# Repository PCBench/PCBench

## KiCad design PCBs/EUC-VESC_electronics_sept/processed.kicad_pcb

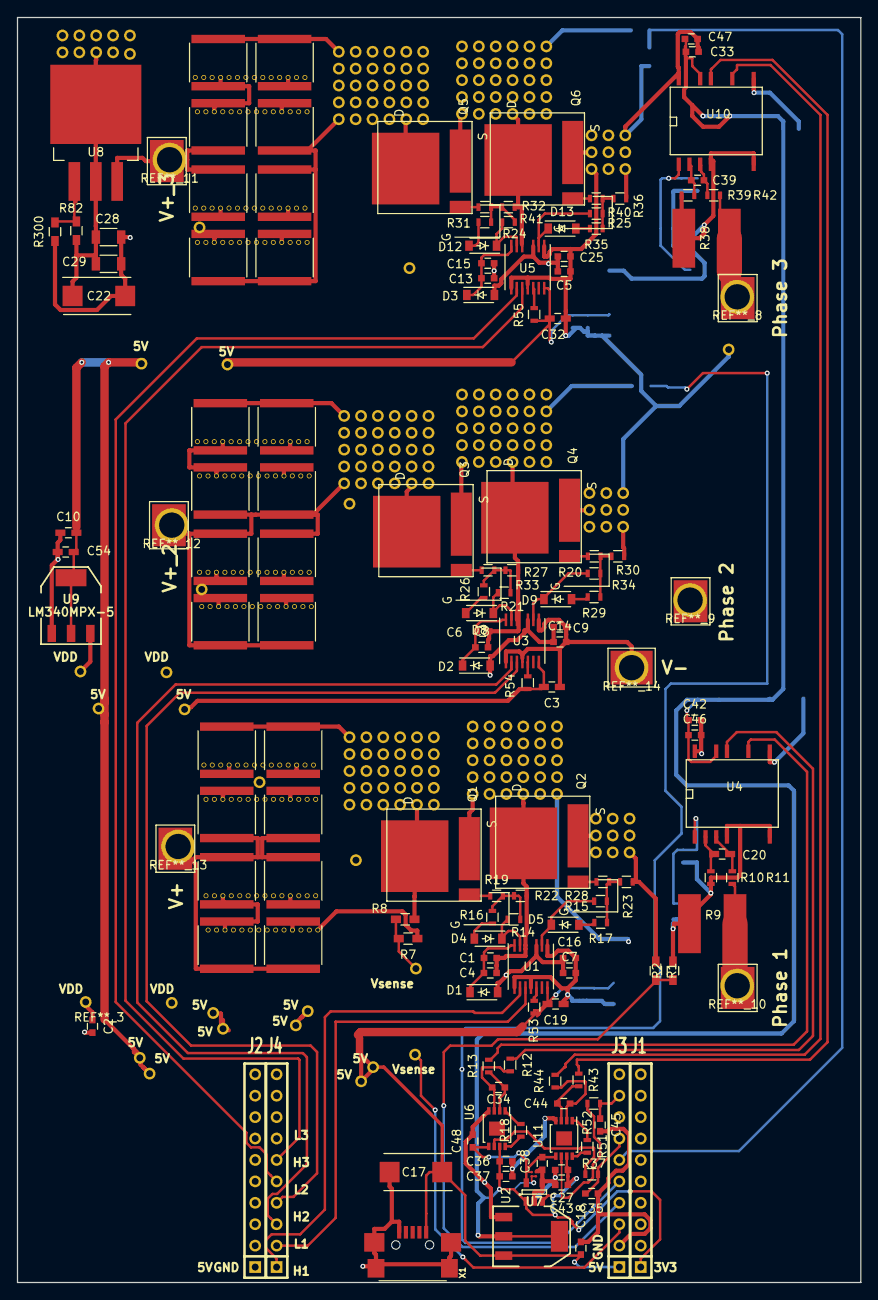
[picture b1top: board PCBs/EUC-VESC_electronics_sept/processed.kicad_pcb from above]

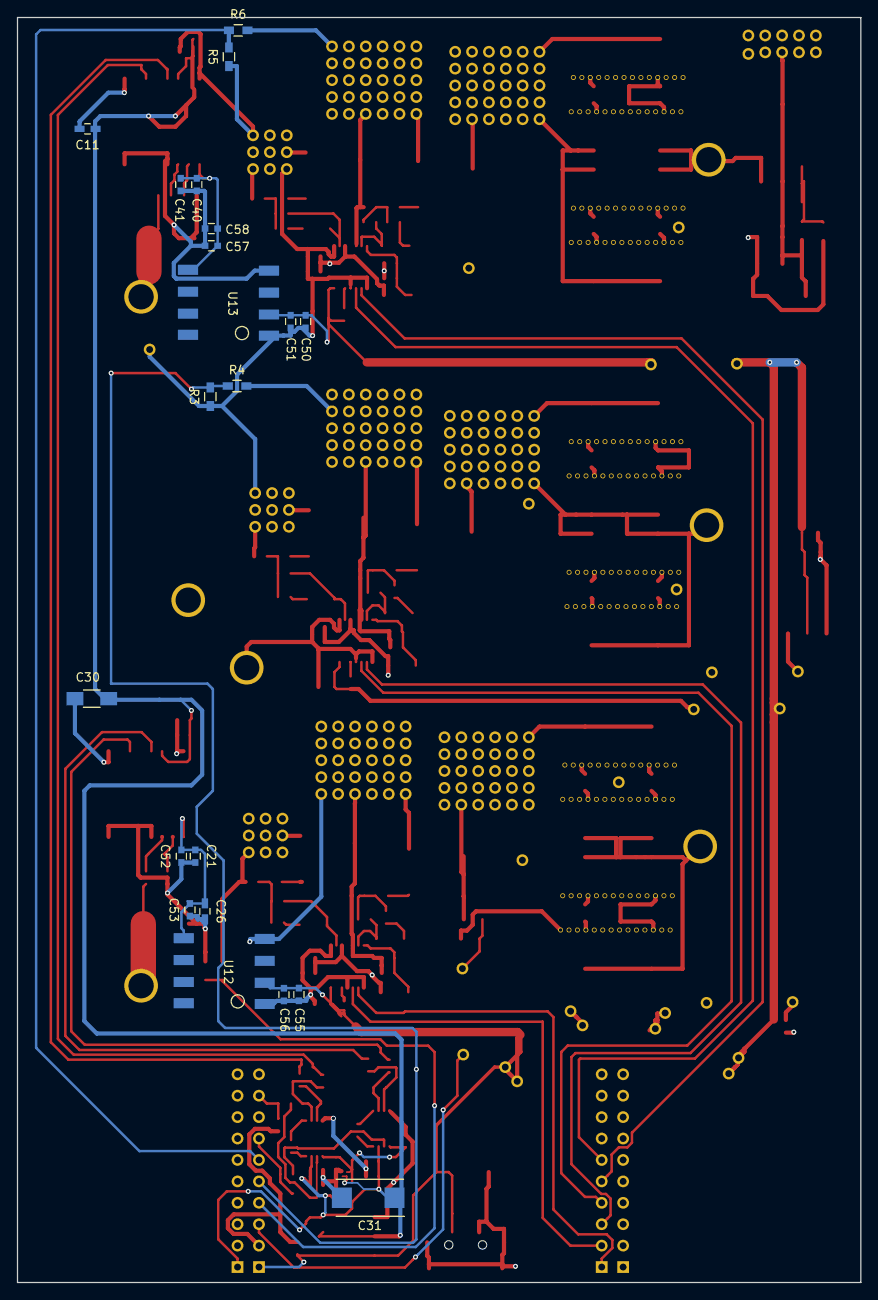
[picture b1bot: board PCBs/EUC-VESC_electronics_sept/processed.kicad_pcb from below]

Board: 4 copper layers, 100.0 x 150.0 mm, 169 parts (21 on the bottom side), 74 nets.

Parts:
C1, C2, C6, C7, C13, C14, C25, C33, C36, C38, C41, C43, C46, C48, C50, C53, C55, C58: 0.1uf; C_0603
C3, C10, C19, C26, C32: 0.1uf; C_0603_HandSoldering
C4, C16: 2.2uf; C_0603
C5, C8, C9, C15: 2.2; C_0603
C11: 1uf; C_0603_HandSoldering
C17, C22, C31: 100uf; TantalC_SizeD_EIA-7343_Reflow
C18, C21, C27, C37, C40, C42, C47, C51, C52, C56, C57: 10uf; C_0603
C20: 33nf; C_0603_HandSoldering
C28, C29: 10uf; C_1206
C30: 2.2uf; C_1206_HandSoldering
C34, C44: 4.7nf; C_0603
C35, C45: 100pf; C_0603
C39: 33nf; C_0603
C49, C49_2, C49_3, C49_4, C49_5, C49_6, C49_7, C49_8, C49_9, C49_10, C49_11, C49_12, C49_13, C49_14, C49_15, C49_16, C49_17, C49_18, C49_19, C49_20, C49_21, C49_22, C49_23, C49_24: 15uf; C_2225_invis
C54: 10uf; C_0603_HandSoldering
D1, D2, D3: DFLS1150-7; SOD-123
D4, D5, D8, D9, D12, D13: D_Schottky_Small; SOD-123
J1: Ti_Booster_40_J1; SIL-10J1
J2: Ti_Booster_40_J2; SIL-10J2
J3: Ti_Booster_40_J3; SIL-10J3
J4: Ti_Booster_40_J4; SIL-10J4
Phase 1: MOTOR3; 1PAD_4x5mm
Phase 2: MOTOR2; 1PAD_4x5mm
Phase 3: MOTOR1; 1PAD_4x5mm
Q1, Q2, Q3, Q4, Q5, Q6: FDMT-800; P-PG-HSOF-08
R1, R3, R5, R7: 1.3K; R_0603_HandSoldering
R2, R4, R6, R8: 39K; R_0603_HandSoldering
R9, R38: 0.001R; shunt_ERJ-MS6SF1M0U
R10, R11, R37, R39, R42, R52: 20R; R_0603
R12, R13, R43, R44: R20; R_0603
R14, R15, R20, R21, R24, R25: 10R; R_0603
R16, R17, R26, R29, R31, R35: R4; R_0603
R18, R51: 10Mr; R_0603
R19, R28, R33, R34, R40, R41: ferrite; R_0603
R22, R23, R27, R30, R32, R36: R39k; R_0603
R53, R54, R55: r20; R_0603
R82: R; R_0603_HandSoldering
R300: R_Small; R_0603_HandSoldering
U1, U3, U5: ADuM7223; LGA-13
U2: TPS72116DBVR; SOT-23-5
U4, U10: SI8920; SI_8920SO-16
U6, U11: ad623; MSOP-8-1EP_3x3mm_Pitch0.65mm
U7: NCP1117ST33T3G; SOT-223
U8: tl783; TO-263-3Lead
U9: LM340MPX-5; SOT223_bcp53
U12, U13: R1SE-0505-R; recom_power
V+: IN+; 1PAD_4x5mm
V+_2, V+_3: IN+; 1PAD_4x5mm
V-: IN-; 1PAD_4x5mm
X1: MINI-USB-SCHIELD-32005-201; USB-UX60R-MB-5ST

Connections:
+1V5: C38.1, C48.1, U2.5, U6.5, U11.5
+3V3: C11.1, C27.1, C30.1, C31.1, C33.1, C36.1, C37.1, C42.1, C43.1, C46.1, C47.1, J1.1, U2.1, U2.3, U4.8, U6.7, U7.2, U10.8, U11.7
+5V: C3.2, C10.2, C17.1, C18.1, C19.2, C32.1, C50.2, C51.2, C54.1, C55.2, C56.2, J3.1, R53.2, R54.2, R55.2, U1.7, U3.7, U5.7, U7.3, U9.3, U12.2, U13.2, X1.1
+5VA: C21.1, C26.1, C52.2, C53.2, U4.1, U12.5
+5VD: C40.1, C41.1, C57.2, C58.2, U10.1, U13.5
/Power MOSFETS/CurrentA: C35.1, J3.7, R37.1
/Power MOSFETS/CurrentC: C45.1, J3.9, R52.1
/Power MOSFETS/H2_VS: C6.2, C8.2, Phase 2.1, Q3.2, Q4.1, R4.2, R27.1, U3.11
/Power MOSFETS/M_H1: J4.1, U1.2
/Power MOSFETS/M_H2: J4.3, U3.2
/Power MOSFETS/M_H3: J4.5, U5.2
/Power MOSFETS/M_L1: J4.2, U1.3
/Power MOSFETS/M_L2: J4.4, U3.3
/Power MOSFETS/M_L3: J4.6, U5.3
/Power MOSFETS/PHASE_1: Phase 1.1, R9.1, R11.2
/Power MOSFETS/PHASE_3: Phase 3.1, R38.1, R42.2
/Power MOSFETS/sense1_N: R13.2, U4.6
/Power MOSFETS/sense1_P: R12.2, U4.7
/Power MOSFETS/sense2_N: R44.2, U10.6
/Power MOSFETS/sense2_P: R43.2, U10.7
GND: C2.2, C3.1, C5.2, C7.2, C9.2, C10.1, C11.2, C14.2, C16.2, C17.2, C18.2, C19.1, C22.2, C25.2, C27.2, C28.1, C29.1, C30.2, C31.2, C32.2, C33.2, C35.2, C36.2, C37.2, C38.2, C42.2, C43.2, C45.2, C46.2, C47.2, C48.2, C49.2, C49_2.2, C49_3.2, C49_4.2, C49_5.2, C49_6.2, C49_7.2, C49_8.2, C49_9.2, C49_10.2, C49_11.2, C49_12.2, C49_13.2, C49_14.2, C49_15.2, C49_16.2, C49_17.2, C49_18.2, C49_19.2, C49_20.2, C49_21.2, C49_22.2, C49_23.2, C49_24.2, C50.1, C51.1, C54.2, C55.1, C56.1, J2.1, J3.2, Q2.2, Q4.2, Q6.2, R1.1, R3.1, R5.1, R7.1, R23.1, R30.1, R36.1, R300.2, U1.1, U1.4, U1.8, U2.2, U2.4, U3.1, U3.4, U3.8, U4.5, U5.1, U5.4, U5.8, U6.4, U7.1, U9.2, U10.5, U11.4, U12.1, U13.1, V-.1, X1.5
GNDA: C1.2, C4.2, C21.2, C26.2, C52.1, C53.1, Q1.2, Q2.1, R2.2, R9.2, R10.2, R22.1, U1.11, U4.4, U12.4
GNDD: C13.2, C15.2, C40.2, C41.2, C57.1, C58.1, Q5.2, Q6.1, R6.2, R32.1, R38.2, R39.2, U5.11, U10.4, U13.4
unnamed: C1.1, C4.1, D1.1, U1.13
unnamed: C6.1, C8.1, D2.1, U3.13
unnamed: C13.1, C15.1, D3.1, U5.13
unnamed: C20.1, R10.1, U4.2
unnamed: C20.2, R11.1, U4.3
unnamed: C34.1, R12.1, U6.3
unnamed: C34.2, R13.1, U6.2
unnamed: C39.1, R39.1, U10.2
unnamed: C39.2, R42.1, U10.3
unnamed: C44.1, R43.1, U11.3
unnamed: C44.2, R44.1, U11.2
unnamed: D4.1, R14.2, U1.12
unnamed: D4.2, R16.2
unnamed: D5.1, R15.1, U1.9
unnamed: D5.2, R17.2
unnamed: D8.1, R21.1, U3.12
unnamed: D8.2, R26.2
unnamed: D9.1, R20.1, U3.9
unnamed: D9.2, R29.2
unnamed: D12.1, R24.1, U5.12
unnamed: D12.2, R31.2
unnamed: D13.1, R25.1, U5.9
unnamed: D13.2, R35.2
unnamed: J3.3, R7.2, R8.1
unnamed: J3.4, R1.2, R2.1
unnamed: J3.5, R3.2, R4.1
unnamed: J3.6, R5.2, R6.1
unnamed: Q1.3, R19.1
unnamed: Q2.3, R28.2
unnamed: Q3.3, R33.1
unnamed: Q4.3, R34.1
unnamed: Q5.3, R41.1
unnamed: Q6.3, R40.1
unnamed: R14.1, R16.1, R19.2, R22.2
unnamed: R15.2, R17.1, R23.2, R28.1
unnamed: R18.1, U6.8
unnamed: R18.2, U6.1
unnamed: R20.2, R29.1, R30.2, R34.2
unnamed: R21.2, R26.1, R27.2, R33.2
unnamed: R24.2, R31.1, R32.2, R41.2
unnamed: R25.2, R35.1, R36.2, R40.2
unnamed: R37.2, U6.6
unnamed: R51.1, U11.8
unnamed: R51.2, U11.1
unnamed: R52.2, U11.6
unnamed: R53.1, U1.5
unnamed: R54.1, U3.5
unnamed: R55.1, U5.5
unnamed: R82.2, R300.1, U8.1
VDD: C2.1, C5.1, C7.1, C9.1, C14.1, C16.1, C22.1, C25.1, C28.2, C29.2, D1.2, D2.2, D3.2, R82.1, U1.10, U3.10, U5.10, U8.2, U8.4, U9.1
V_SUPPLY: C49.1, C49_2.1, C49_3.1, C49_4.1, C49_5.1, C49_6.1, C49_7.1, C49_8.1, C49_9.1, C49_10.1, C49_11.1, C49_12.1, C49_13.1, C49_14.1, C49_15.1, C49_16.1, C49_17.1, C49_18.1, C49_19.1, C49_20.1, C49_21.1, C49_22.1, C49_23.1, C49_24.1, Q1.1, Q3.1, Q5.1, R8.2, U8.3, V+.1, V+_2.1, V+_3.1

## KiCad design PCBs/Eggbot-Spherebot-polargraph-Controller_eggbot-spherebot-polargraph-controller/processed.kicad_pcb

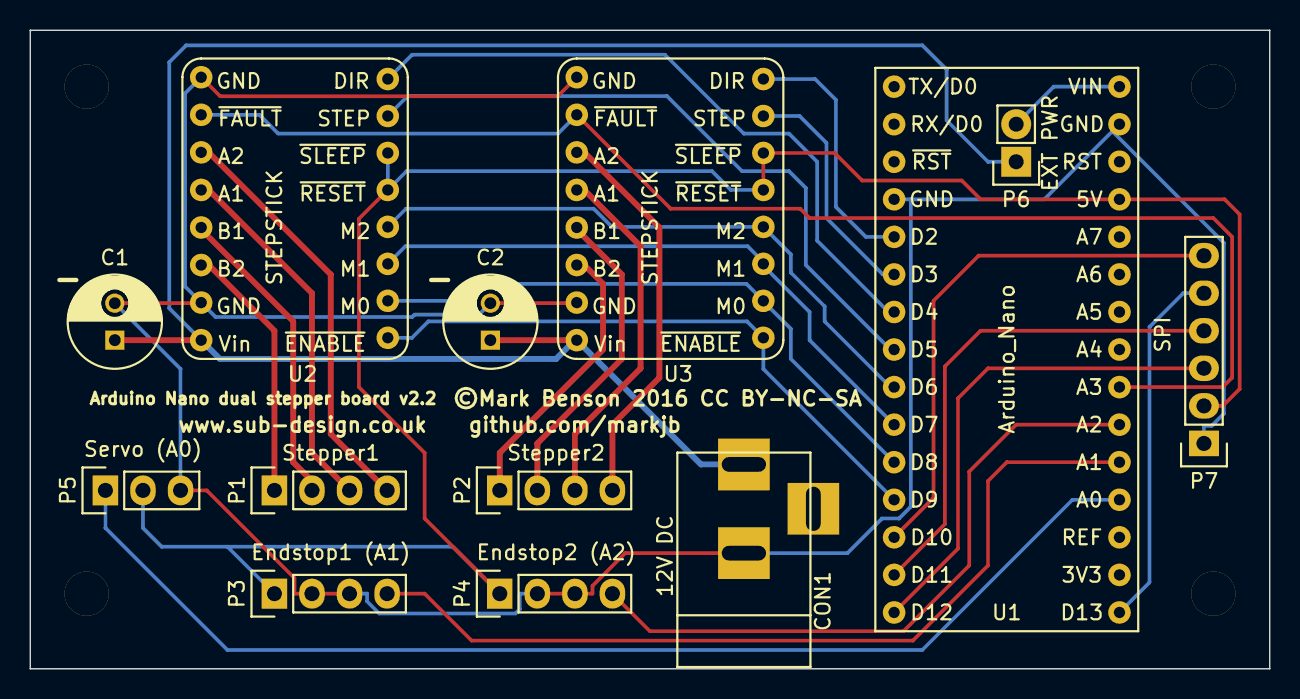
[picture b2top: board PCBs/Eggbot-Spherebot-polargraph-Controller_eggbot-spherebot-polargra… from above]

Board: 2 copper layers, 83.8 x 43.2 mm, 13 parts (0 on the bottom side), 28 nets.

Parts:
C1, C2: CP; C_Radial_D6.3_L11.2_P2.5
CON1: 12V DC; BARREL_JACK
P1: Stepper1; Pin_Header_Straight_1x04
P2: Stepper2; Pin_Header_Straight_1x04
P3: Endstop1 (A1); Pin_Header_Straight_1x04
P4: Endstop2 (A2); Pin_Header_Straight_1x04
P5: Servo (A0); Pin_Header_Straight_1x03
P6: EXT PWR; Pin_Header_Straight_1x02
P7: SPI; Pin_Header_Straight_1x06
U1: Arduino_Nano; Arduino_nano_v3
U2, U3: STEPSTICK; Stepstick

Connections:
+12V: C1.1, C2.1, CON1.1, P6.1, U2.8, U3.8
/DIR1: U1.7, U2.16
/DIR2: U1.5, U3.16
/ENABLE: U1.12, U2.9, U3.9
/ESTOP1: P3.4, U1.20
/ESTOP2: P4.4, U1.21
/FAULT: U1.22, U2.2, U3.2
/M0: U1.11, U2.10, U3.10
/M1: U1.10, U2.11, U3.11
/M2: U1.9, U2.12, U3.12
/MISO: P7.3, U1.15
/MOSI: P7.4, U1.14
/SCK: P7.5, U1.16
/SD_SEL: P7.6, U1.13
/SERVO: P5.1, U1.19
/STEP1: U1.8, U2.15
/STEP2: U1.6, U3.15
/VCC: P3.1, P4.1, P5.2, P7.2, U1.27, U2.13, U2.14, U3.13, U3.14
GND: C1.2, C2.2, CON1.2, P3.2, P3.3, P4.2, P4.3, P5.3, P7.1, U1.4, U1.29, U2.1, U2.7, U3.1, U3.7
unnamed: P1.1, U2.6
unnamed: P1.2, U2.5
unnamed: P1.3, U2.4
unnamed: P1.4, U2.3
unnamed: P2.1, U3.6
unnamed: P2.2, U3.5
unnamed: P2.3, U3.4
unnamed: P2.4, U3.3
unnamed: P6.2, U1.30

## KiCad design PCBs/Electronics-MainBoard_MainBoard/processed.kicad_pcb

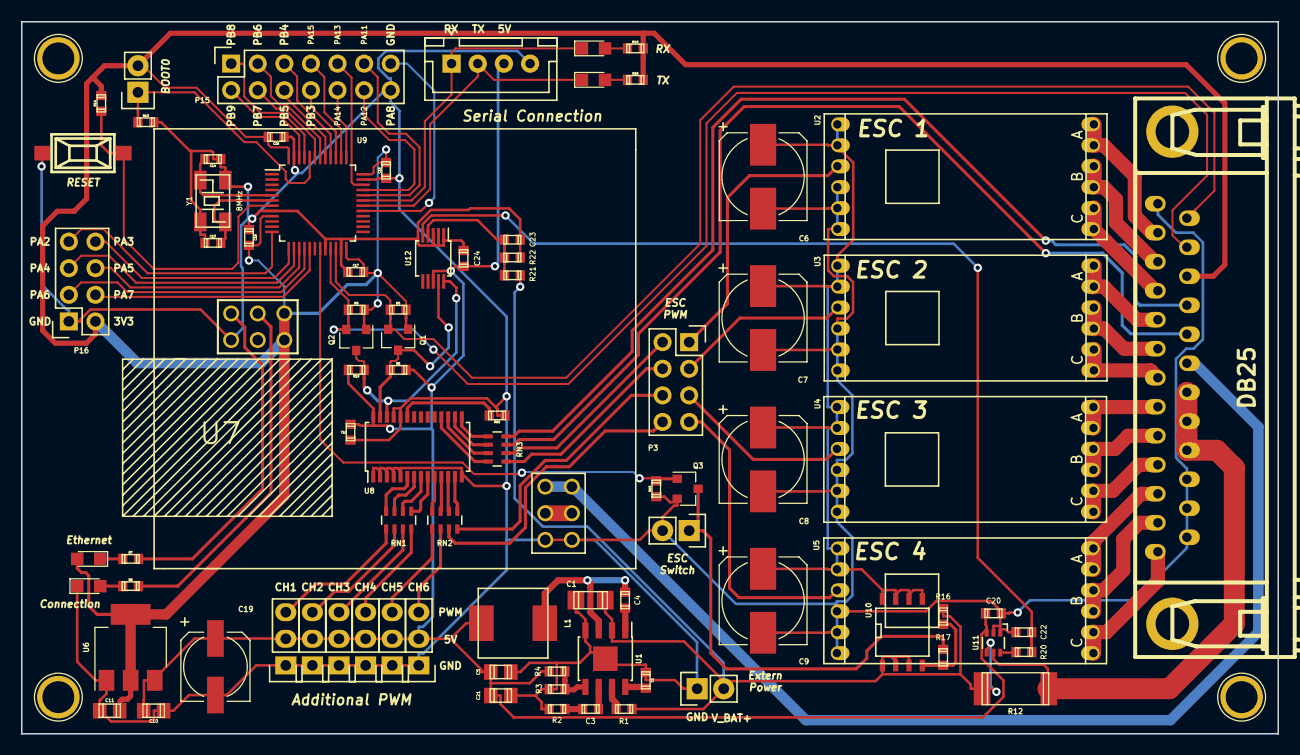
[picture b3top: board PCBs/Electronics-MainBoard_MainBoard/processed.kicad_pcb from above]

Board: 2 copper layers, 120.0 x 68.0 mm, 89 parts (0 on the bottom side), 96 nets.

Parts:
C1: 10uF/25V; c_1206
C2, C20, C23, C24: 0.1uF; c_0603
C3: 3.9nF; c_0603
C4: 10nF; c_0603
C5, C21: 22uF/10V; c_0805
C6, C7, C8, C9: 220uF/25V; CP_Elec_8x10
C10, C11: 1uF; c_0805
C12: 10uF; c_0603
C13, C14: 33pF; c_0603
C15, C16, C17, C18, C22: 1uF; c_0603
C19: 220uF/10V; CP_Elec_6.3x5.8
D1, D2, D3, D4: LED; LED_0805
J1: DB25; DB_25M
L1: 10uH/4A; ASPI-0630LR
P1: BOOT; Socket_Strip_Straight_1x02
P2: CONN_01X04; JST_XH_B04B-XH-A_04x2.50mm_Straight
P3, P16: CONN_02X04; Socket_Strip_Straight_2x04
P4, P5, P6, P7: HOLE; 1pin
P8, P14: CONN_01X02; Socket_Strip_Straight_1x02
P9, P10, P11, P12, P13, P18: CONN_01X03; Socket_Strip_Straight_1x03
P15: CONN_02X07; Socket_Strip_Straight_2x07
Q1, Q2: BSS138; SOT-23
Q3: DMN65D8L; SOT-23
R1: 100k; r_0603
R2: 6.8k; r_0603
R3: 10k 1%; r_0603
R4: 44.2k 1%; r_0603
R5, R8, R9, R10, R11, R13, R14, R15, R16: 10k; r_0603
R6, R7, R18, R19: 330; r_0603
R12: 0.003 %1; r_2512
R17: 1k; r_0603
R20: 3.3k; r_0603
R21: 30.1k %1; r_0603
R22: 10k %1; r_0603
RN1, RN2, RN3: 20k; R_Array_Concave_4x0603
SW1: RESET; smd_push
U1: mp2307; SOIC-8-1EP_3.9x4.9mm_Pitch1.27mm
U2, U3, U4, U5: DYS_mini_ESC; DYS_Mini_ESC
U6: TLV1117LV33; SOT-223
U7: TENDA_P200; Tenda_p200
U8: pca9685; TSSOP-28_4.4x9.7mm_Pitch0.65mm
U9: STM32F103CBT6; LQFP-48_7x7mm_Pitch0.5mm
U10: SI4425DDY; SOIC-8-N
U11: INA199A2; SC-70-6
U12: ADS1015; MSOP-10_3x3mm_Pitch0.5mm
Y1: 8MHz; crystal_maple

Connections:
/3V3: C11.1, C15.1, C16.1, C17.1, C18.1, D2.2, J1.23, P1.2, P16.2, Q1.1, Q2.1, R5.1, R9.1, R14.1, R18.1, R19.1, U6.2, U6.4, U7.3V3, U9.9, U9.24, U9.36, U9.48
/5V: C5.1, C10.1, C12.1, C19.1, C20.1, C21.1, C24.1, L1.2, P2.3, P9.2, P10.2, P11.2, P12.2, P13.2, P18.2, R4.1, R8.1, R10.1, U6.3, U8.28, U11.3, U12.8
/ADC_I: C22.1, R20.1, U12.5
/ADC_V: C23.1, R21.2, R22.1, U12.4
/CH0: P9.3, RN1.1
/CH1: P10.3, RN1.2
/CH2: P11.3, RN1.3
/CH3: P12.3, RN1.4
/CH4: P13.3, RN2.1
/CH5: P18.3, RN2.2
/CH6: P3.8, RN2.3
/CH7: P3.6, RN2.4
/CH10: P3.2, RN3.6
/CH11: P3.4, RN3.5
/ESC1: P3.1, U2.2
/ESC2: P3.3, U3.2
/ESC3: P3.5, U4.2
/ESC4: P3.7, U5.2
/LED1: J1.21, RN3.7
/LED2: J1.22, RN3.8
/MOTOR_1A: J1.12, U2.4
/MOTOR_1B: J1.11, U2.5
/MOTOR_1C: J1.10, U2.6
/MOTOR_2A: J1.9, U3.4
/MOTOR_2B: J1.8, U3.5
/MOTOR_2C: J1.7, U3.6
/MOTOR_3A: J1.6, U4.4
/MOTOR_3B: J1.5, U4.5
/MOTOR_3C: J1.4, U4.6
/MOTOR_4A: J1.3, U5.4
/MOTOR_4B: J1.2, U5.5
/MOTOR_4C: J1.1, U5.6
/OSC_N: C14.1, U9.5, Y1.2
/OSC_P: C13.1, U9.6, Y1.1
/PA2: P16.7, U9.12
/PA3: P16.8, U9.13
/PA4: P16.5, U9.14
/PA5: P16.6, U9.15
/PA6: P16.3, U9.16
/PA7: P16.4, U9.17
/PA8: P15.13, U9.29
/PA11: P15.11, U9.32
/PA12: P15.12, U9.33
/PA13: P15.9, U9.34
/PA14: P15.10, U9.37
/PA15: P15.7, U9.38
/PB3: P15.8, U9.39
/PB4: P15.5, U9.40
/PB5: P15.6, U9.41
/PB6: P15.3, U9.42
/PB7: P15.4, U9.43
/PB8: P15.1, U9.45
/PB9: P15.2, U9.46
/PWR_SW: Q3.1, R15.1, U9.19
/RX1: D4.1, P2.1, U9.31
/SCL_3V3: J1.24, Q2.2, R9.2, U9.21
/SCL_5V: Q2.3, R10.2, U8.26, U12.10
/SDA_3V3: J1.25, Q1.2, R5.2, U9.22
/SDA_5V: Q1.3, R8.2, U8.27, U12.9
/T+: J1.20, U7.T_+
/TX1: D3.1, P2.2, U9.30
/V_BAT: C1.1, P8.2, R1.1, R12.1, R16.1, R21.1, U1.2, U10.1, U10.2, U10.3, U11.4
/V_IN: J1.17, J1.18, J1.19, R12.2, U11.5
/V_PWR: C6.1, C7.1, C8.1, C9.1, U2.3, U3.3, U4.3, U5.3, U10.5, U10.6, U10.7, U10.8
GND: C1.2, C2.2, C5.2, C6.2, C7.2, C8.2, C9.2, C10.2, C11.2, C12.2, C13.2, C14.2, C15.2, C16.2, C17.2, C18.2, C19.2, C20.2, C21.2, C22.2, C23.2, C24.2, D1.1, J1.13, J1.14, J1.15, J1.16, P2.4, P8.1, P9.1, P10.1, P11.1, P12.1, P13.1, P14.2, P15.14, P16.1, P18.1, Q3.2, R2.2, R3.2, R11.2, R13.1, R15.2, R22.2, SW1.1, U1.4, U1.9, U2.1, U3.1, U4.1, U5.1, U6.1, U7.GND, U7.T_-, U8.1, U8.2, U8.3, U8.4, U8.5, U8.14, U8.24, U8.25, U9.8, U9.20, U9.23, U9.35, U9.47, U11.1, U11.2, U12.1, U12.2, U12.3, Y1.3
unnamed: C2.1, U1.8
unnamed: C3.1, U1.6
unnamed: C3.2, R2.1
unnamed: C4.1, L1.1, U1.3
unnamed: C4.2, U1.1
unnamed: D1.2, R6.2
unnamed: D2.1, R7.2
unnamed: D3.2, R18.2
unnamed: D4.2, R19.2
unnamed: P1.1, R13.2, U9.44
unnamed: P14.1, Q3.3, R17.2
unnamed: R1.2, U1.7
unnamed: R3.1, R4.2, U1.5
unnamed: R6.1, U7.C
unnamed: R7.1, U7.E
unnamed: R11.1, U8.23
unnamed: R14.2, SW1.2, U9.7
unnamed: R16.2, R17.1, U10.4
unnamed: R20.2, U11.6
unnamed: RN1.5, U8.9
unnamed: RN1.6, U8.8
unnamed: RN1.7, U8.7
unnamed: RN1.8, U8.6
unnamed: RN2.5, U8.13
unnamed: RN2.6, U8.12
unnamed: RN2.7, U8.11
unnamed: RN2.8, U8.10
unnamed: RN3.1, U8.15
unnamed: RN3.2, U8.16
unnamed: RN3.3, U8.17
unnamed: RN3.4, U8.18

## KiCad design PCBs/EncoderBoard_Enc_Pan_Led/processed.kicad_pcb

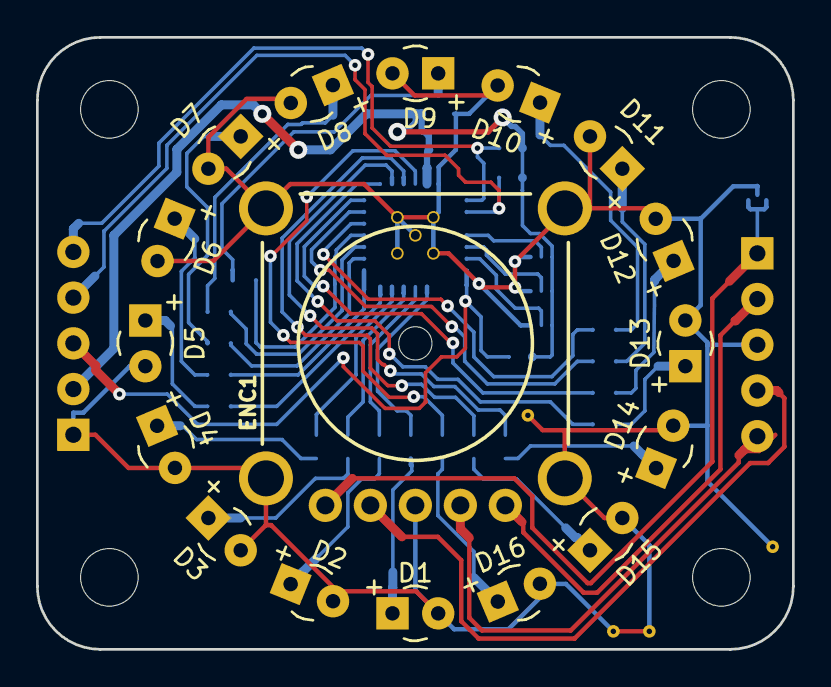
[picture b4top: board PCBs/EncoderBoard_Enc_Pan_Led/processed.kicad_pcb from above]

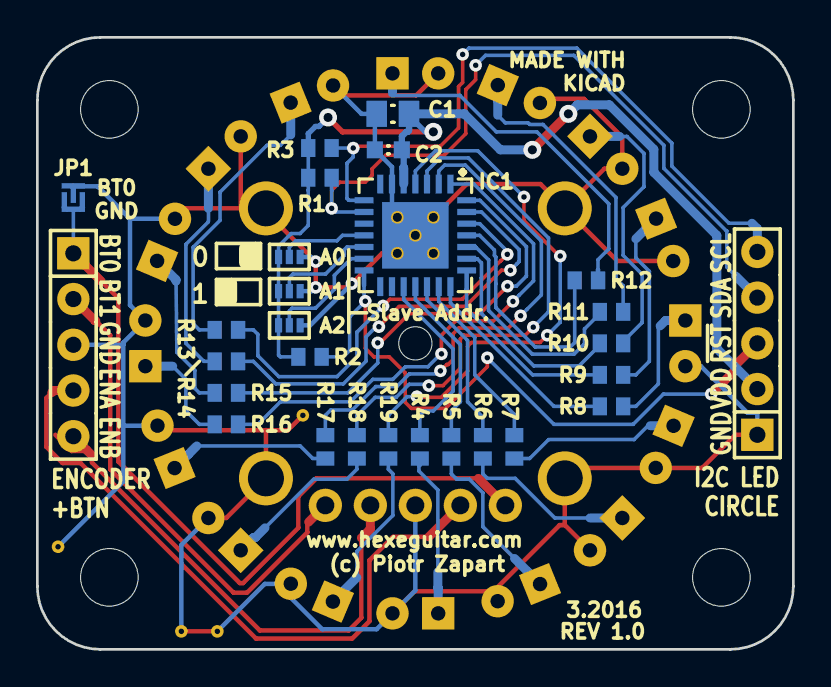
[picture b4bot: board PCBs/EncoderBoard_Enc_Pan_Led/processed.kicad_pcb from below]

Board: 2 copper layers, 42.0 x 34.0 mm, 58 parts (28 on the bottom side), 44 nets.

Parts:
C1: 10µ; CAPC_0805_2012X70N
C2: 100n; CAPC_0603_1608X55N
D1, D2, D3, D4, D5, D6, D7, D8, D9, D10, D11, D12, D13, D14, D15, D16: LED; Diode_LED_3mm_round_vertical
ENC1: Panasonic_EVEP_encoder; PanasonicEVEP_Encoder
IC1: MCP23017_QFN; QFN65P600X600X100-29VN
JP1: Jumper_NO_Small; PCB_jumper_2
MP1, MP2, MP3, MP4: SCREW; MountingHole_3-5mm
P1, P2: CONN_01X05; 1x5_254
R1, R3: 2k2; RESC_0603_1508X63N
R2: 10k; RESC_0603_1508X63N
R4, R5, R6, R7, R8, R9, R10, R11, R12, R13, R14, R15, R16, R17, R18, R19: R; RESC_0603_1508X63N
SW1, SW2, SW3: PCB_SPDT; SPDT_BlobSwitch_SMD
Via0703_GND, Via0703_GND_2, Via0703_GND_3, Via0703_GND_4, Via0703_GND_5, Via0703_GND_6, Via0703_GND_7, Via0703_GND_8, Via0703_GND_9: VAL**; Via0703_GND

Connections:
/BTN0: ENC1.1, JP1.1, P1.1
/BTN1: ENC1.5, P1.2
/ENC_A: ENC1.2, P1.4
/ENC_B: ENC1.4, P1.5
/LED0: IC1.17, R4.2
/LED1: IC1.18, R5.2
/LED2: IC1.19, R6.2
/LED3: IC1.20, R7.2
/LED4: IC1.21, R8.2
/LED5: IC1.22, R9.2
/LED6: IC1.23, R10.2
/LED7: IC1.24, R11.2
/LED8: IC1.25, R12.2
/LED9: IC1.26, R13.2
/LED10: IC1.27, R14.2
/LED11: IC1.28, R15.2
/LED12: IC1.1, R16.2
/LED13: IC1.2, R17.2
/LED14: IC1.3, R18.2
/LED15: IC1.4, R19.2
/SCL: IC1.8, P2.5, R3.1
/SDA: IC1.9, P2.4, R1.1
/VDD: C1.1, C2.1, IC1.5, P2.2, R1.2, R2.2, R3.2, SW1.3, SW2.3, SW3.3
/~RESET: IC1.14, P2.3, R2.1
GND: C1.2, C2.2, D1.2, D2.2, D3.2, D4.2, D5.2, D6.2, D7.2, D8.2, D9.2, D10.2, D11.2, D12.2, D13.2, D14.2, D15.2, D16.2, ENC1.3, ENC1.6, ENC1.7, ENC1.8, ENC1.9, IC1.6, IC1.29, JP1.2, P1.3, P2.1, SW1.1, SW2.1, SW3.1, Via0703_GND.1, Via0703_GND_2.1, Via0703_GND_3.1, Via0703_GND_4.1, Via0703_GND_5.1, Via0703_GND_6.1, Via0703_GND_7.1, Via0703_GND_8.1, Via0703_GND_9.1
unnamed: D1.1, R4.1
unnamed: D2.1, R5.1
unnamed: D3.1, R6.1
unnamed: D4.1, R7.1
unnamed: D5.1, R8.1
unnamed: D6.1, R9.1
unnamed: D7.1, R10.1
unnamed: D8.1, R11.1
unnamed: D9.1, R12.1
unnamed: D10.1, R13.1
unnamed: D11.1, R14.1
unnamed: D12.1, R15.1
unnamed: D13.1, R16.1
unnamed: D14.1, R17.1
unnamed: D15.1, R18.1
unnamed: D16.1, R19.1
unnamed: IC1.11, SW1.2
unnamed: IC1.12, SW2.2
unnamed: IC1.13, SW3.2

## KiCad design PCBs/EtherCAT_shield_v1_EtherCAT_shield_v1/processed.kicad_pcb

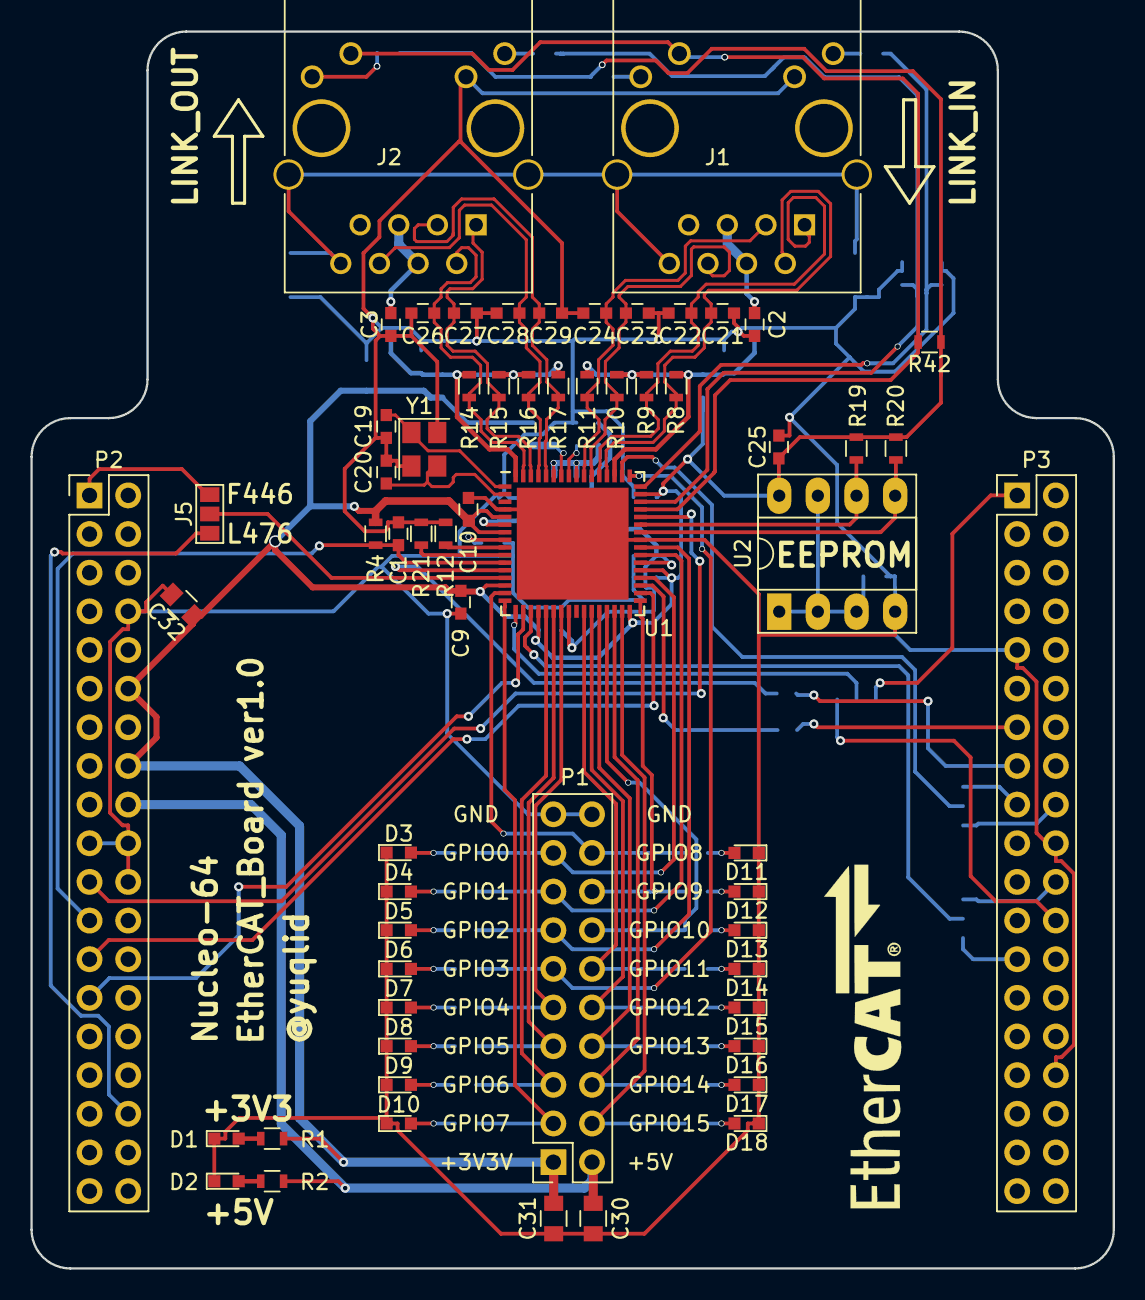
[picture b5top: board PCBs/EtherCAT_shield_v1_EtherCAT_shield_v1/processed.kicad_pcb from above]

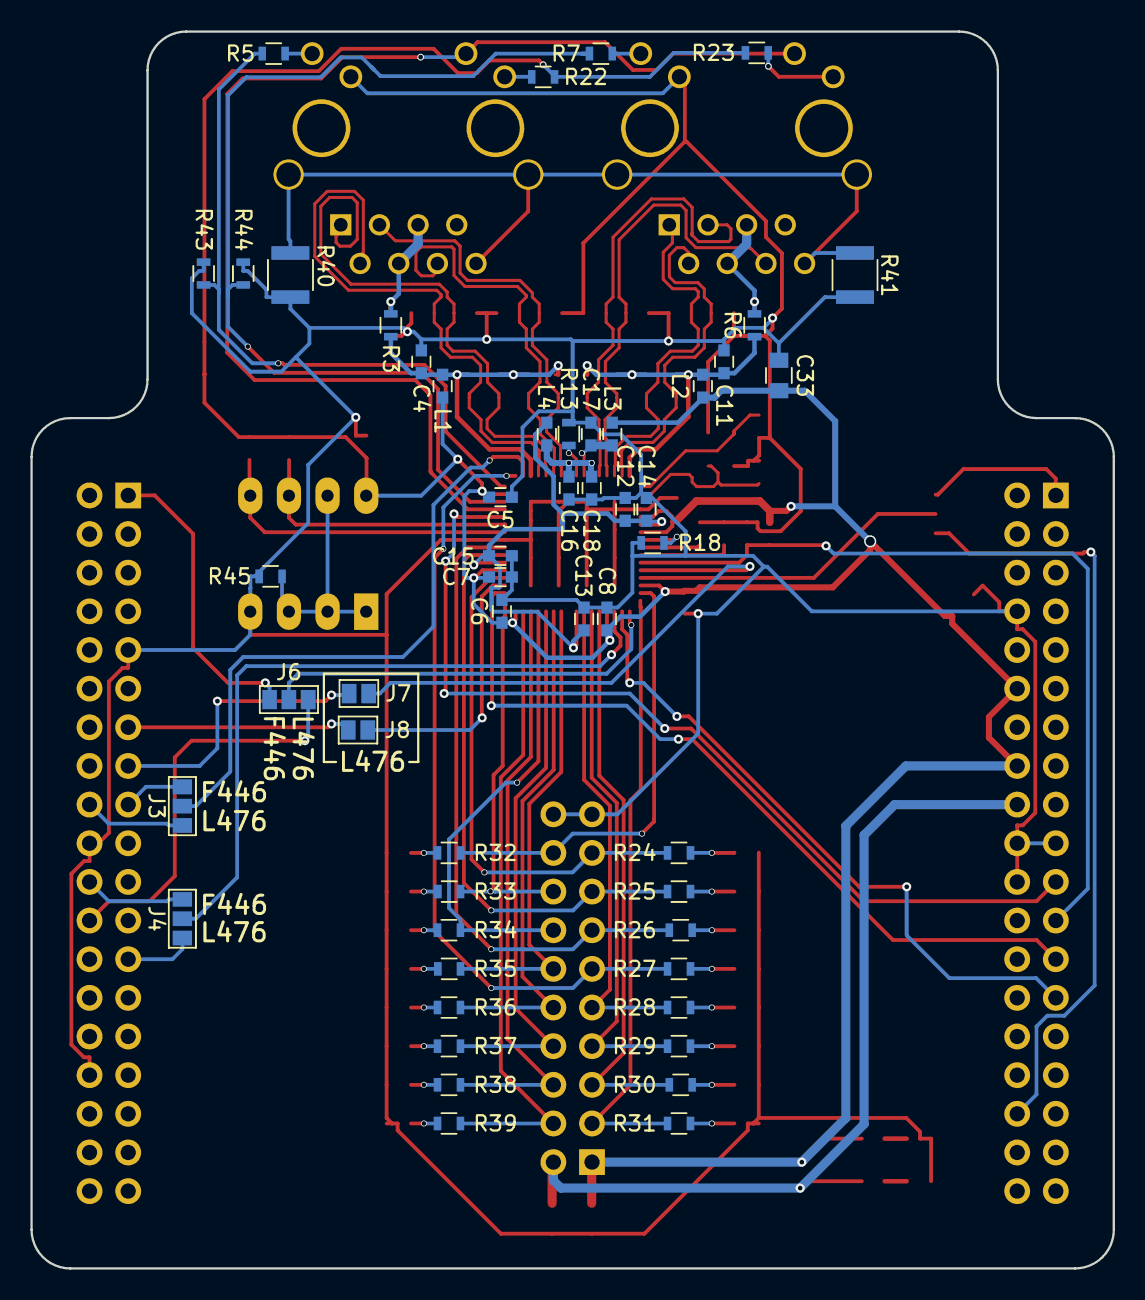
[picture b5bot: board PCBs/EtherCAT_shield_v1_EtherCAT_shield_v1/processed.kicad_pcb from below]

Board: 2 copper layers, 71.1 x 81.3 mm, 114 parts (52 on the bottom side), 89 nets.

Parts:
C1, C4, C5, C6, C7, C8, C9, C10, C11, C14, C15, C16, C17, C18, C25: 0.1u; C_0603
C2, C3: 0.022u; C_0603
C12: 1u; C_0603
C13: 470p; C_0603
C19, C20: C; C_0603
C21, C22, C23, C24, C26, C27, C28, C29: 10p; C_0603
C30, C31, C32, C33: 10u; C_0805
D1, D2, D3, D4, D5, D6, D7, D8, D9, D10, D11, D12, D13, D14, D15, D16, D17, D18: LED; LED_0603
J1, J2: RJ45-PULSETRANS; RJ45_J0011D21BNL
J3, J4, J5, J6: GS3
J7, J8: GS2
L1, L2, L3, L4: L; C_0603
P1: CONN_02X10; Socket_Strip_Straight_2x10_Pitch2.54mm
P2, P3: CONN_02X19; Pin_Header_Straight_2x19_Pitch2.54mm
R1, R2: R; R_0603
R3, R6: 0; R_0603
R4, R12, R18, R21, R42, R43, R44: 10k; R_0603
R5, R7, R22, R23: 330; R_0603
R8, R9, R10, R11, R14, R15, R16, R17: 49.9; R_0603
R13: 12.1k; R_0603
R19, R20: 2k; R_0603
R24, R25, R26, R27, R28, R29, R30, R31, R32, R33, R34, R35, R36, R37, R38, R39: 1k; R_0603
R40, R41: R; R_1210
R45: 4.7k; R_0603
U1: LAN9252; QFN-64-1EP_9x9mm_Pitch0.5mm
U2: 24LC00; DIP-8_W7.62mm_Socket_LongPads
Y1: Crystal_GND24; Crystal_SMD_Abracon_ABM8G-4pin_3.2x2.5mm

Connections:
+3V3: C5.1, C6.1, C7.1, C8.1, C9.1, C10.1, C25.1, C31.1, C32.1, C33.1, L1.1, L2.1, L3.1, P1.1, P2.12, P2.16, R1.1, R4.1, R19.1, R20.1, R22.1, R23.1, R42.1, U1.5, U1.7, U1.14, U1.20, U1.32, U1.37, U1.47, U2.8
+5V: C30.1, P1.2, P2.18, R2.1
/LAN9252/LINKACTLED0: R5.1, R43.1, U1.48
/LAN9252/LINKACTLED1: R7.1, R44.1, U1.46
/LAN9252/RUNLED: J1.11, J2.11, R42.2, U1.45
/LAN9252/VDD33TXRX1: C4.1, L1.2, R3.2, R8.2, R9.2, R10.2, R11.2, U1.51
/LAN9252/VDDTXRX2: C11.1, L2.2, R6.1, R14.2, R15.2, R16.2, R17.2, U1.64
GND: C1.2, C2.2, C3.2, C4.2, C5.2, C6.2, C7.2, C8.2, C9.2, C10.2, C11.2, C12.2, C13.2, C14.2, C15.2, C16.2, C17.2, C18.2, C19.2, C20.2, C21.2, C22.2, C23.2, C24.2, C25.2, C26.2, C27.2, C28.2, C29.2, C30.2, C31.2, C32.2, C33.2, D1.1, D2.1, D3.1, D4.1, D5.1, D6.1, D7.1, D8.1, D9.1, D10.1, D11.1, D12.1, D13.1, D14.1, D15.1, D16.1, D17.1, D18.1, J1.10, J2.10, P1.19, P1.20, P2.8, P2.19, P2.20, P2.22, P3.9, P3.20, P3.32, R12.2, R13.2, R18.2, R21.2, R40.2, R41.2, R43.2, R44.2, R45.2, U1.4, U1.41, U1.65, U2.4, Y1.2, Y1.4
GNDPWR: J1.8, J1.13, J1.14, J2.8, J2.13, J2.14, R40.1, R41.1
GPIO0: P1.17, R24.2, U1.36
GPIO1: P1.15, R25.2, U1.39
GPIO2: P1.13, R26.2, U1.40
GPIO3: P1.11, R27.2, U1.49
GPIO4: P1.9, R28.2, U1.23
GPIO5: P1.7, R29.2, U1.22
GPIO6: P1.5, R30.2, U1.21
GPIO7: P1.3, R31.2, U1.16
GPIO8: P1.18, R32.2, U1.15
GPIO9: P1.16, R33.2, U1.33
GPIO10: P1.14, R34.2, U1.29
GPIO11: P1.12, R35.2, U1.26
GPIO12: P1.10, R36.2, U1.27
GPIO13: P1.8, R37.2, U1.28
GPIO14: P1.6, R38.2, U1.30
GPIO15: P1.4, R39.2, U1.31
LAN9252_IRQ: P2.21, U1.44
LAN9252_RST: C1.1, P2.23, R4.2, U1.11
unnamed: C2.1, J1.4, J1.5, R3.1
unnamed: C3.1, J2.4, J2.5, R6.2
unnamed: C12.1, C13.1, C14.1, C15.1, L4.1, U1.6, U1.24, U1.38
unnamed: C16.1, C18.1, L4.2, U1.56, U1.59
unnamed: C17.1, L3.2, U1.58
unnamed: C19.1, U1.1, Y1.1
unnamed: C20.1, U1.2, Y1.3
unnamed: D1.2, R1.2
unnamed: D2.2, R2.2
unnamed: D3.2, R24.1
unnamed: D4.2, R25.1
unnamed: D5.2, R26.1
unnamed: D6.2, R27.1
unnamed: D7.2, R28.1
unnamed: D8.2, R29.1
unnamed: D9.2, R30.1
unnamed: D10.2, R31.1
unnamed: D11.2, R32.1
unnamed: D12.2, R33.1
unnamed: D13.2, R34.1
unnamed: D14.2, R35.1
unnamed: D15.2, R36.1
unnamed: D16.2, R37.1
unnamed: D17.2, R38.1
unnamed: D18.2, R39.1
unnamed: J1.9, R5.2
unnamed: J1.12, R22.2
unnamed: J2.9, R7.2
unnamed: J2.12, R23.2
unnamed: R12.1, U1.9
unnamed: R13.1, U1.57
unnamed: R18.1, U1.8
unnamed: R19.2, U1.43, U2.6
unnamed: R20.2, U1.42, U2.5
unnamed: R21.1, U1.10
unnamed: R45.1, U2.1, U2.2, U2.3, U2.7
PA6: J8.2, P3.13
PA7: J7.2, P3.15
PB0: J5.3, P2.34
PB1: J6.3, P3.24
PB2: J4.1, P3.22
PB6: J3.1, P3.17
PB10: J4.3, P3.25
PB11: J3.3, P3.18
PC9: J6.1, P3.1
PC10: J5.1, P2.1
RX1_N: C23.1, J1.6, R10.1, U1.54
RX1_P: C24.1, J1.3, R11.1, U1.55
RX2_N: C28.1, J2.6, R16.1, U1.61
RX2_P: C29.1, J2.3, R17.1, U1.60
SCK: J4.2, U1.19
SIO0: J6.2, U1.17
SIO1: J5.2, U1.13
SIO2: J7.1, U1.12
SIO3: J8.1, U1.35
SYNC0: P2.25, U1.34
SYNC1: P2.27, U1.18
TX1_N: C21.1, J1.2, R8.1, U1.52
TX1_P: C22.1, J1.1, R9.1, U1.53
TX2_N: C26.1, J2.2, R14.1, U1.63
TX2_P: C27.1, J2.1, R15.1, U1.62
~SCS: J3.2, U1.50

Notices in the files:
PCBs/Eggbot-Spherebot-polargraph-Controller_eggbot-spherebot-polargraph-controller/processed.kicad_pcb:
©Mark Benson 2016 CC BY-NC-SA
